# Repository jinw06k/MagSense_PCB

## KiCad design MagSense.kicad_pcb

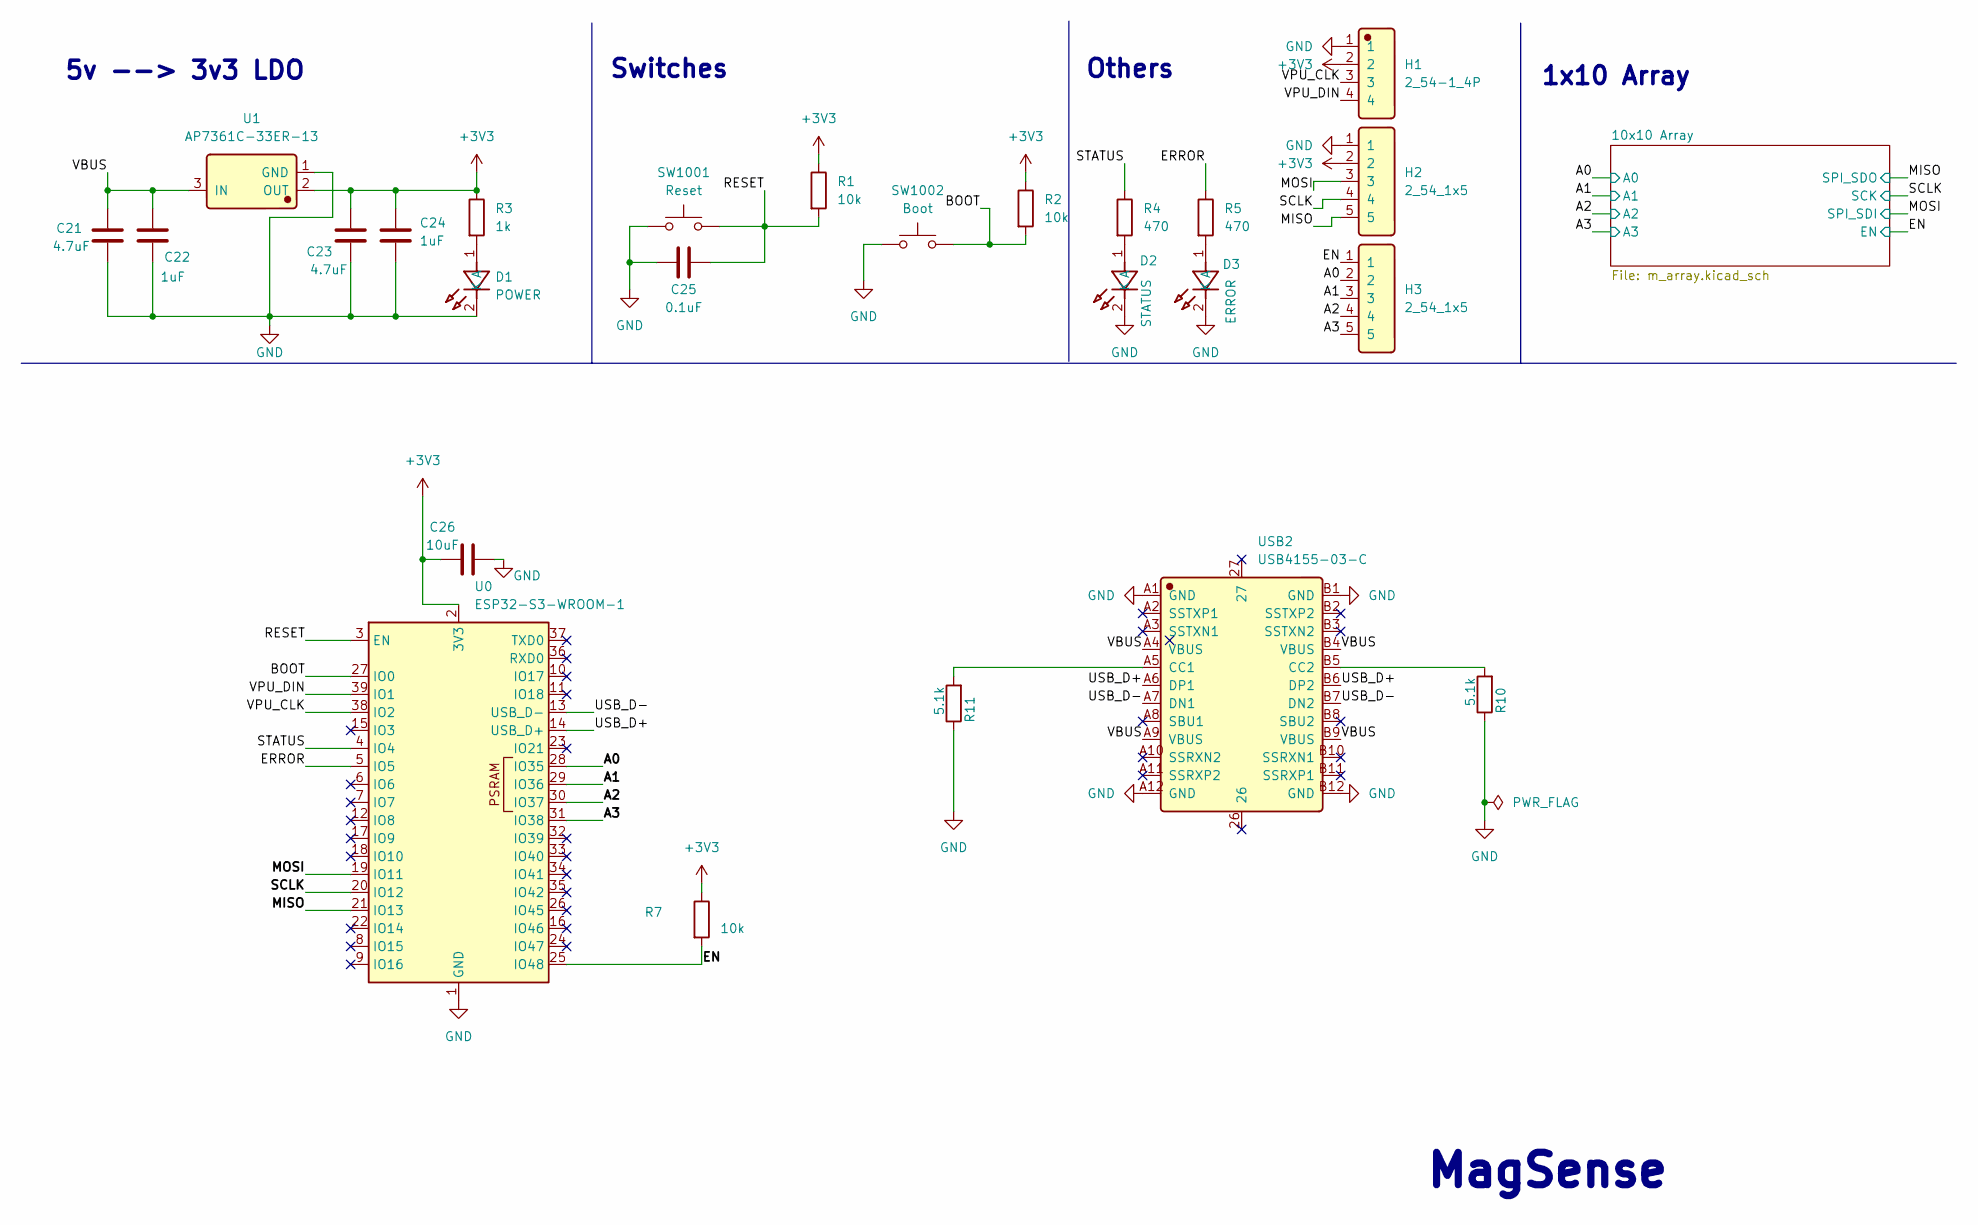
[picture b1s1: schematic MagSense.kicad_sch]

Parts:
C21, C23: 4.7uF; C_0805_2012Metric
C22, C24: 1uF; C_0603_1608Metric
C25: 0.1uF; C_0603_1608Metric
C26: 10uF; C_0805_2012Metric
D1: POWER; 19-217_R6C-AL1M2VY_6T; Manufacturer Part 19-217/GHC-YR1S2/6T; LCSC C2986059
D2: STATUS; 19-217_R6C-AL1M2VY_6T; Manufacturer Part 19-217/BHC-ZL1M2RY/6T; LCSC C2986058
D3: ERROR; 19-217_R6C-AL1M2VY_6T; Manufacturer Part 19-217/R6C-AL1M2VY/6T; LCSC C2986060
H1: 2_54-1_4P; Manufacturer Part 2.54-1*4P母; LCSC C2718488
H2, H3: 2_54_1x5; Header-Female-2_54_1x5; Manufacturer Part 2.54-1*5P母; LCSC C50950
R1, R2, R7: 10k; R_0603_1608Metric
R3: 1k; R_0603_1608Metric
R4, R5: 470; R_0603_1608Metric
R10, R11: 5.1k; R_0603_1608Metric
SW1001: Reset; SW_SPST_PTS810; LCSC C116501
SW1002: Boot; SW_SPST_PTS810; LCSC C116501
U0: ESP32-S3-WROOM-1; LCSC C2913198
U1: AP7361C-33ER-13; Manufacturer Part AP7361C-33ER-13; LCSC C3743528
USB2: USB4155-03-C; Manufacturer Part USB4155-03-C; LCSC C5183853

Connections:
+3V3: C23.1, C24.1, C26.1, H1.2, H2.2, R1.1, R2.1, R3.1, R7.1, U0.2 (3V3), U1.2 (OUT); also elsewhere on the board
/A0: H3.2, U0.28 (IO35); also elsewhere on the board
/A1: H3.3, U0.29 (IO36); also elsewhere on the board
/A2: H3.4, U0.30 (IO37); also elsewhere on the board
/A3: H3.5, U0.31 (IO38); also elsewhere on the board
/BOOT: R2.2, SW1002.2, U0.27 (IO0)
/EN: H3.1, R7.2, U0.25 (IO48); also elsewhere on the board
/ERROR: R5.1, U0.5 (IO5)
/MISO: H2.5, U0.21 (IO13); also elsewhere on the board
/MOSI: H2.3, U0.19 (IO11); also elsewhere on the board
/RESET: C25.1, R1.2, SW1001.2, U0.3 (EN)
/SCLK: H2.4, U0.20 (IO12); also elsewhere on the board
/STATUS: R4.1, U0.4 (IO4)
/USB_D+: U0.14 (USB_D+), USB2.A6 (DP1), USB2.B6 (DP2)
/USB_D-: U0.13 (USB_D-), USB2.A7 (DN1), USB2.B7 (DN2)
/VBUS: C21.1, C22.1, U1.3 (IN), USB2.A4 (VBUS), USB2.A9 (VBUS), USB2.B4 (VBUS), USB2.B9 (VBUS)
/VPU_CLK: H1.3, U0.38 (IO2)
/VPU_DIN: H1.4, U0.39 (IO1)
GND: C21.2, C22.2, C23.2, C24.2, C25.2, C26.2, D1.2 (K), D2.2 (K), D3.2 (K), H1.1, H2.1, R10.1, R11.1, SW1001.1, SW1002.1, U0.1 (GND), U0.40 (GND), U0.41 (GND), U1.1 (GND), USB2.A1 (GND), USB2.A12 (GND), USB2.B1 (GND), USB2.B12 (GND); also elsewhere on the board
unnamed: D1.1 (A), R3.2
unnamed: D2.1 (A), R4.2
unnamed: D3.1 (A), R5.2
unnamed: R11.2, USB2.A5 (CC1)
unnamed: R10.2, USB2.B5 (CC2)

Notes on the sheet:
5v --> 3v3 LDO
1x10 Array
Others
MagSense
Switches

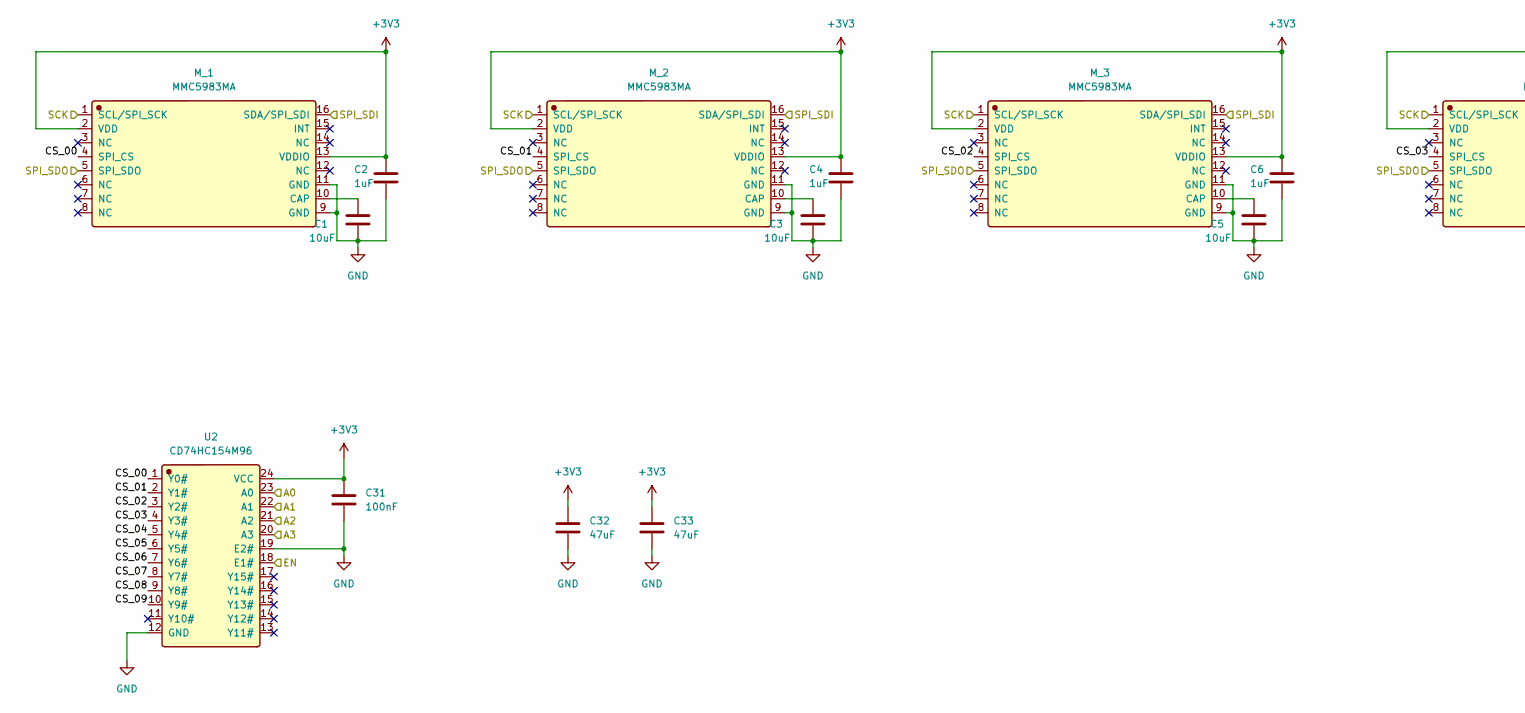
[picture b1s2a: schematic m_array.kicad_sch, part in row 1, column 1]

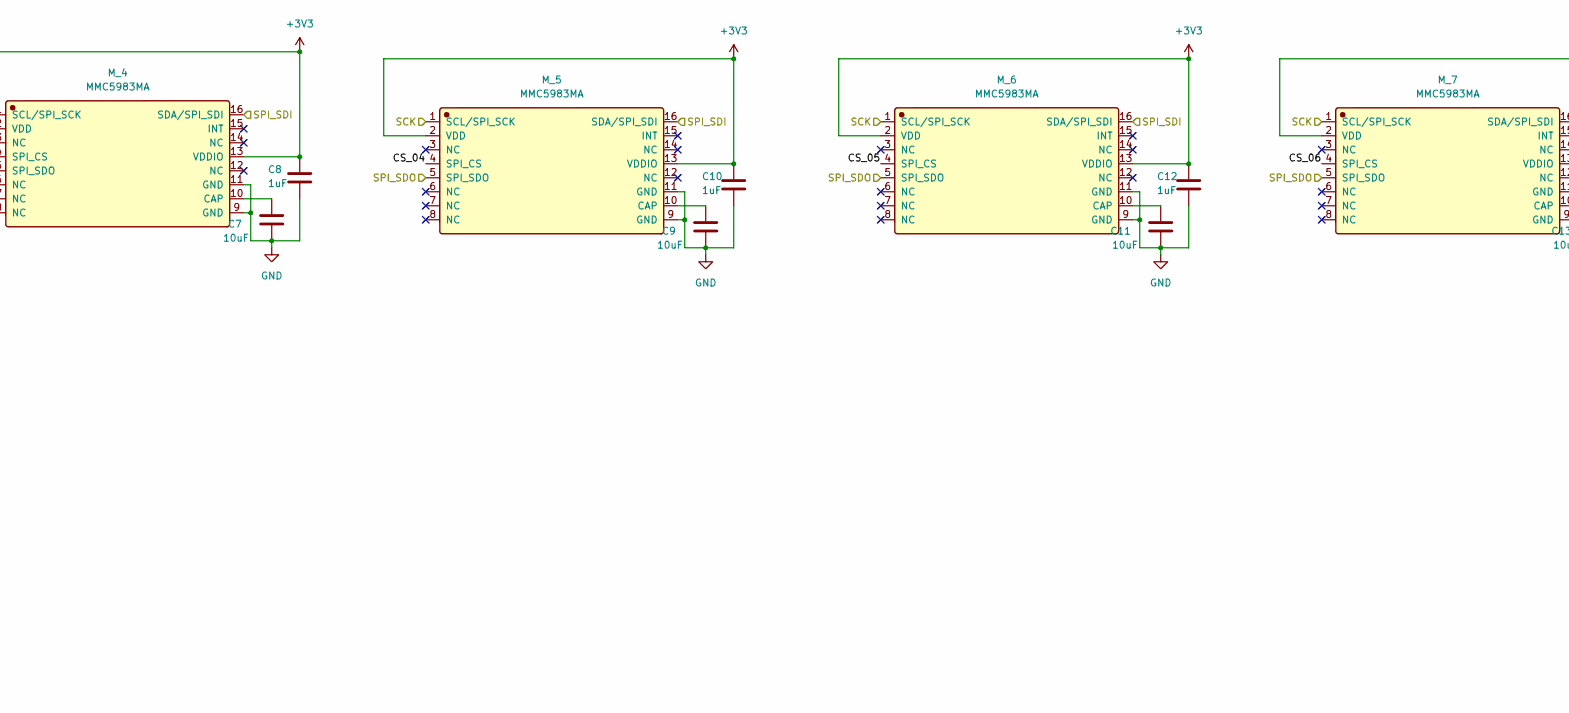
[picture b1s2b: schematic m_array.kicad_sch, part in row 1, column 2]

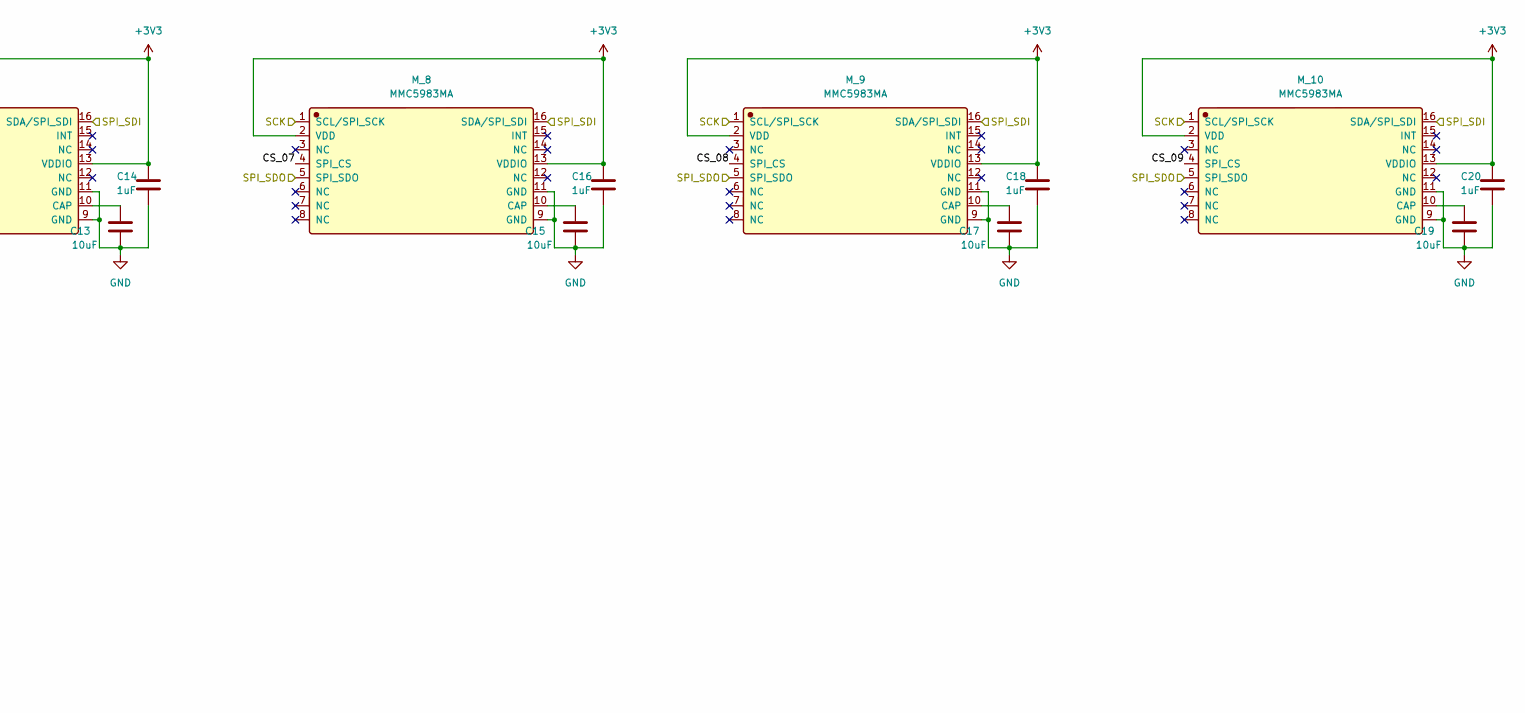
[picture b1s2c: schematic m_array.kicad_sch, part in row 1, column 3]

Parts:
C1, C3, C5, C7, C9, C11, C13, C15, C17, C19: 10uF; C_0805_2012Metric
C2, C4, C6, C8, C10, C12, C14, C16, C18, C20: 1uF; C_0603_1608Metric
C31: 100nF; C_0603_1608Metric
C32, C33: 47uF; C_1206_3216Metric
M_1, M_2, M_3, M_4, M_5, M_6, M_7, M_8, M_9, M_10: MMC5983MA; PARTREV A; LCSC C404329
U2: CD74HC154M96; Manufacturer Part CD74HC154M96; LCSC C2832236

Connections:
+3V3: C2.1, C4.1, C6.1, C8.1, C10.1, C12.1, C14.1, C16.1, C18.1, C20.1, C31.1, C32.1, C33.1, M_1.2 (VDD), M_1.13 (VDDIO), M_2.2 (VDD), M_2.13 (VDDIO), M_3.2 (VDD), M_3.13 (VDDIO), M_4.2 (VDD), M_4.13 (VDDIO), M_5.2 (VDD), M_5.13 (VDDIO), M_6.2 (VDD), M_6.13 (VDDIO), M_7.2 (VDD), M_7.13 (VDDIO), M_8.2 (VDD), M_8.13 (VDDIO), M_9.2 (VDD), M_9.13 (VDDIO), M_10.2 (VDD), M_10.13 (VDDIO), U2.24 (VCC); also elsewhere on the board
/10x10 Array/CS_00: M_1.4 (SPI_CS), U2.1 (Y0#)
/10x10 Array/CS_01: M_2.4 (SPI_CS), U2.2 (Y1#)
/10x10 Array/CS_02: M_3.4 (SPI_CS), U2.3 (Y2#)
/10x10 Array/CS_03: M_4.4 (SPI_CS), U2.4 (Y3#)
/10x10 Array/CS_04: M_5.4 (SPI_CS), U2.5 (Y4#)
/10x10 Array/CS_05: M_6.4 (SPI_CS), U2.6 (Y5#)
/10x10 Array/CS_06: M_7.4 (SPI_CS), U2.7 (Y6#)
/10x10 Array/CS_07: M_8.4 (SPI_CS), U2.8 (Y7#)
/10x10 Array/CS_08: M_9.4 (SPI_CS), U2.9 (Y8#)
/10x10 Array/CS_09: M_10.4 (SPI_CS), U2.10 (Y9#)
/A0: U2.23 (A0); also elsewhere on the board
/A1: U2.22 (A1); also elsewhere on the board
/A2: U2.21 (A2); also elsewhere on the board
/A3: U2.20 (A3); also elsewhere on the board
/EN: U2.18 (E1#); also elsewhere on the board
/MISO: M_1.5 (SPI_SDO), M_2.5 (SPI_SDO), M_3.5 (SPI_SDO), M_4.5 (SPI_SDO), M_5.5 (SPI_SDO), M_6.5 (SPI_SDO), M_7.5 (SPI_SDO), M_8.5 (SPI_SDO), M_9.5 (SPI_SDO), M_10.5 (SPI_SDO); also elsewhere on the board
/MOSI: M_1.16 (SDA/SPI_SDI), M_2.16 (SDA/SPI_SDI), M_3.16 (SDA/SPI_SDI), M_4.16 (SDA/SPI_SDI), M_5.16 (SDA/SPI_SDI), M_6.16 (SDA/SPI_SDI), M_7.16 (SDA/SPI_SDI), M_8.16 (SDA/SPI_SDI), M_9.16 (SDA/SPI_SDI), M_10.16 (SDA/SPI_SDI); also elsewhere on the board
/SCLK: M_1.1 (SCL/SPI_SCK), M_2.1 (SCL/SPI_SCK), M_3.1 (SCL/SPI_SCK), M_4.1 (SCL/SPI_SCK), M_5.1 (SCL/SPI_SCK), M_6.1 (SCL/SPI_SCK), M_7.1 (SCL/SPI_SCK), M_8.1 (SCL/SPI_SCK), M_9.1 (SCL/SPI_SCK), M_10.1 (SCL/SPI_SCK); also elsewhere on the board
GND: C1.2, C2.2, C3.2, C4.2, C5.2, C6.2, C7.2, C8.2, C9.2, C10.2, C11.2, C12.2, C13.2, C14.2, C15.2, C16.2, C17.2, C18.2, C19.2, C20.2, C31.2, C32.2, C33.2, M_1.9 (GND), M_1.11 (GND), M_2.9 (GND), M_2.11 (GND), M_3.9 (GND), M_3.11 (GND), M_4.9 (GND), M_4.11 (GND), M_5.9 (GND), M_5.11 (GND), M_6.9 (GND), M_6.11 (GND), M_7.9 (GND), M_7.11 (GND), M_8.9 (GND), M_8.11 (GND), M_9.9 (GND), M_9.11 (GND), M_10.9 (GND), M_10.11 (GND), U2.12 (GND), U2.19 (E2#); also elsewhere on the board
unnamed: C1.1, M_1.10 (CAP)
unnamed: C3.1, M_2.10 (CAP)
unnamed: C5.1, M_3.10 (CAP)
unnamed: C7.1, M_4.10 (CAP)
unnamed: C9.1, M_5.10 (CAP)
unnamed: C11.1, M_6.10 (CAP)
unnamed: C13.1, M_7.10 (CAP)
unnamed: C15.1, M_8.10 (CAP)
unnamed: C17.1, M_9.10 (CAP)
unnamed: C19.1, M_10.10 (CAP)

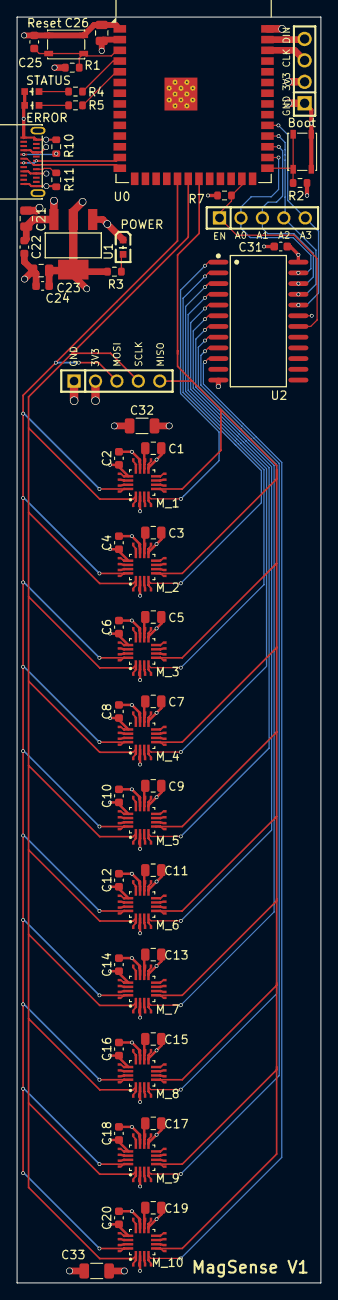
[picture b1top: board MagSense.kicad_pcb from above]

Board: 4 copper layers, 36.0 x 150.0 mm, 59 parts (0 on the bottom side), 44 nets.

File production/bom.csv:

Designator,Footprint,Quantity,Value,LCSC Part #
"C1, C11, C13, C15, C17, C19, C26, C3, C5, C7, C9",805,11,10uF,C117956
"C10, C12, C14, C16, C18, C2, C20, C22, C24, C4, C6, C8",603,12,1uF,C77046
"C21, C23",805,2,4.7uF,C1779
C25,603,1,0.1uF,C77055
C31,603,1,100nF,C77055
"C32, C33",1206,2,47uF,C403725
D1,19-217_R6C-AL1M2VY_6T,1,POWER,C2986059
D2,19-217_R6C-AL1M2VY_6T,1,STATUS,C2986058
D3,19-217_R6C-AL1M2VY_6T,1,ERROR,C2986060
H1,2_54-1_4P,1,2_54-1_4P,C2718488
"H2, H3",Header-Female-2_54_1x5,2,2_54_1x5,C50950
"M_1, M_10, M_2, M_3, M_4, M_5, M_6, M_7, M_8, M_9",MMC5983MA,10,MMC5983MA,C404329
"R1, R2, R7",603,3,10k,C98220
"R10, R11",603,2,5.1k,C2907044
R3,603,1,1k,C21190
"R4, R5",603,2,470,C114669
SW1001,SW_SPST_PTS810,1,Reset,C116501
SW1002,SW_SPST_PTS810,1,Boot,C116501
U0,ESP32-S3-WROOM-1,1,ESP32-S3-WROOM-1,C2913198
U1,AP7361C-33E-13,1,AP7361C-33E-13,C500795
U2,CD74HC154M96,1,CD74HC154M96,C2832236
USB2,USB4155-03-C,1,USB4155-03-C,C5183853
